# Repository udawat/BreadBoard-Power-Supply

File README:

This repository contains EAGLE CAD files of BreadBoard Power Supply from Explore Labs.

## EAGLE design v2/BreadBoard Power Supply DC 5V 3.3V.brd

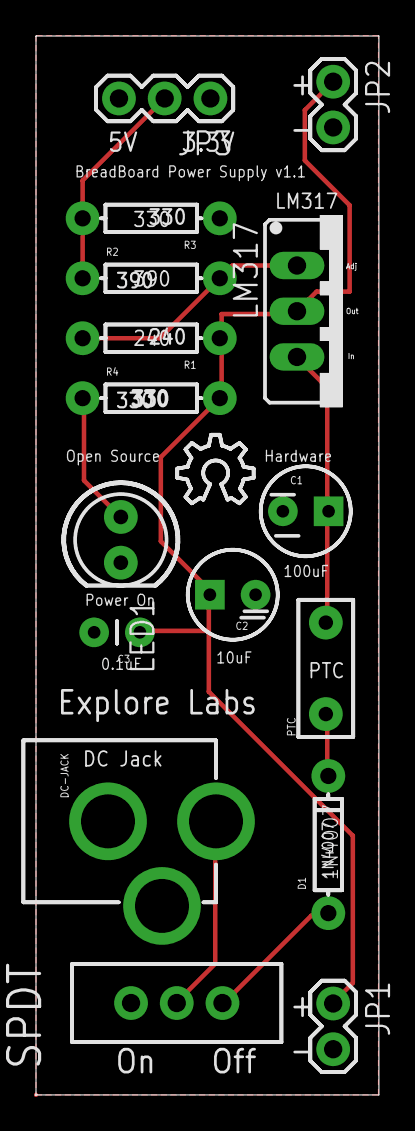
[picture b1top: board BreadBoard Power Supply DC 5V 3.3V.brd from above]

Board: 2 copper layers, 19.1 x 58.8 mm, 17 parts (0 on the bottom side), 9 nets.

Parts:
C1: 100uF; CPOL-RADIAL-10UF-25V
C2: 10uF; CPOL-RADIAL-10UF-25V
C3: 0.1uF; CAP-PTH-SMALL
D1: 1N4007; DIODE-1N4148
DC-JACK: Vin = 7V-12V; POWER_JACK_PTH
JP1, JP2: 1X02
JP3: 1X03
LED1: Power On; LED5MM
LM317: 317TS
LOGO1: OSHW_LOGO_8MILX0150-NT; OSHW_8X150_NOTEXT
PTC: 250mA; PTC
R1: 240; AXIAL-0.3
R2: 390; AXIAL-0.3
R3, R4: 330; AXIAL-0.3
SPDT: On/Off Switch; SWITCH-SPDT

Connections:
GND: C1.2, C2.2, C3.2, DC-JACK.GND, DC-JACK.GNDBREAK, JP1.2, JP2.2, JP3.1, LED1.K, R3.P$1
unnamed: C1.1, LM317.3, PTC.P$2
unnamed: DC-JACK.PWR, SPDT.2
unnamed: D1.A, SPDT.3
unnamed: LM317.1, R1.P$2, R2.P$2
unnamed: JP3.2, R2.P$1, R3.P$2
unnamed: LED1.A, R4.P$1
unnamed: D1.C, PTC.P$1
VCC: C2.1, C3.1, JP1.1, JP2.1, LM317.2, R1.P$1, R4.P$2

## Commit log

2012-11-22 ReadMe
2012-11-22 abrupt commit
2012-11-22 BBPS version 1
    The first ever CAD Design by Explore Labs - A BreadBoard Power Supply
    capable of providing 5V or 3.3V to a BreadBoard
2012-11-22 moved to Gerber Data
2012-11-22 playing around
2012-11-22 new versions added
2012-11-22 moving folders
2012-11-22 included .gitignore
2012-11-22 A good .gitignore file
2012-11-22 deleted .DS_Store
2012-11-22 README update!
